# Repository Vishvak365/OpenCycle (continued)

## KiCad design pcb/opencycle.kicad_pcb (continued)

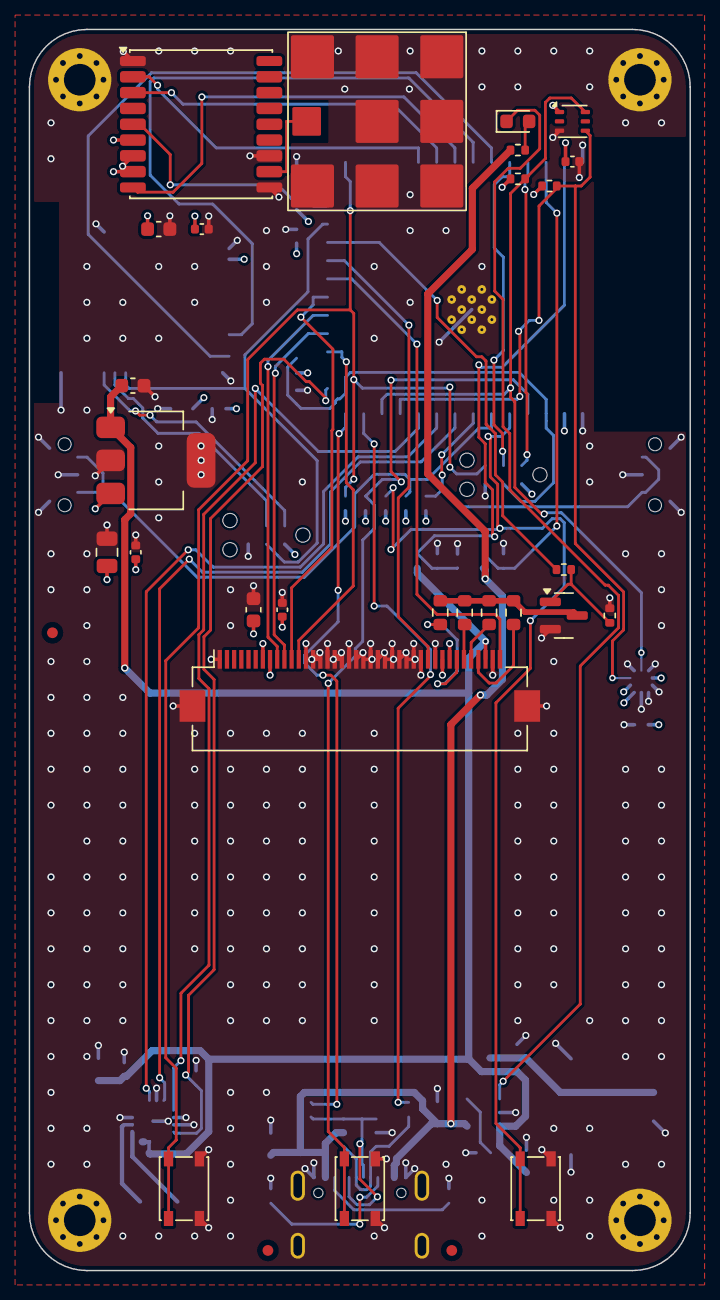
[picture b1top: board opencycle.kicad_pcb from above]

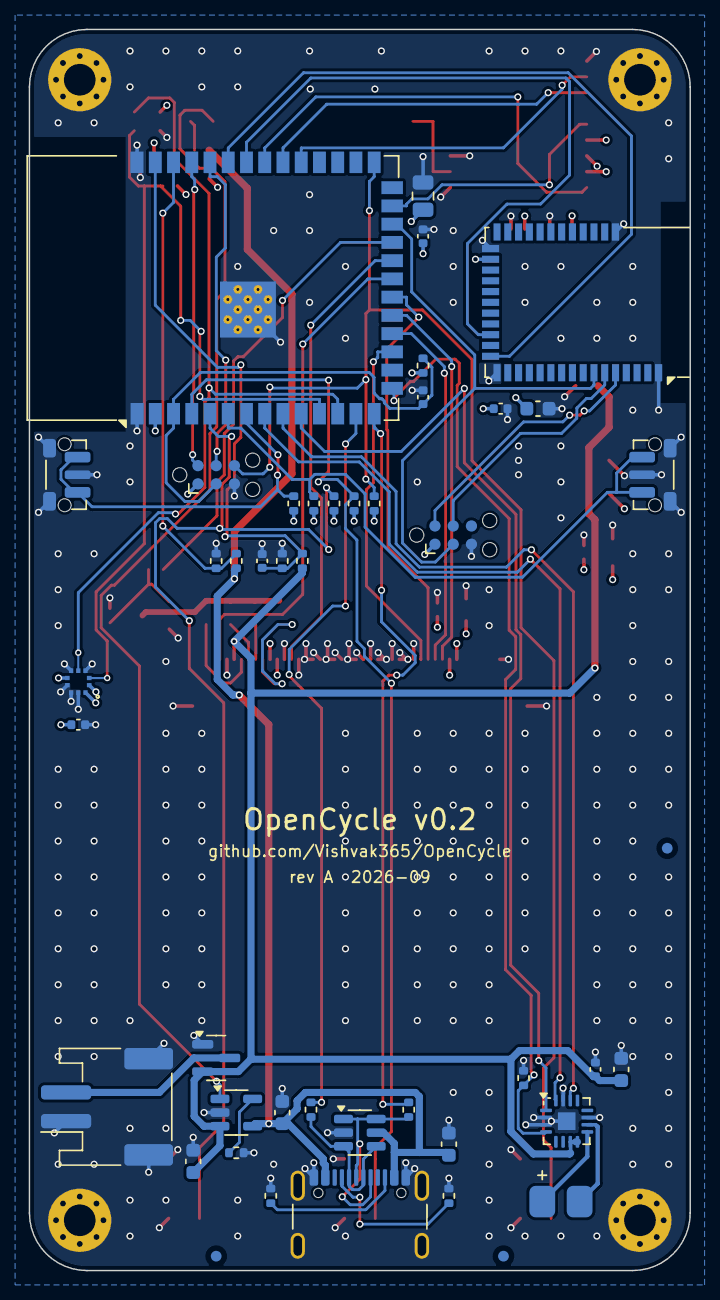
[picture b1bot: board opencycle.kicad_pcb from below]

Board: 4 copper layers, 46.0 x 86.4 mm, 79 parts (45 on the bottom side), 55 nets.

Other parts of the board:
FID1, FID2, FID3, FID4, FID5, FID6: Fiducial; Fiducial_0.75mm_Mask1.5mm
H1, H2, H3, H4: MountingHole_2.2mm_M2_Pad_Via

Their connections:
GND: H1.1, H2.1, H3.1, H4.1; also elsewhere on the board

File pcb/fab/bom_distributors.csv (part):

Vendor,Vendor part number,Manufacturer,MPN,Description,Qty per board,Qty to order (5 boards),Unit price USD,Line total (1 board),Price checked,Stock seen,Designators,Link,Datasheet
Mouser,485-258,,,"Adafruit 258 LiPo 1200 mAh 34 x 62 x 5 mm, protected, JST-PH",1,5,9.95,9.95,2026-09-30,,"checked 2026-09-30, 388 in stock",,
Mouser,621-AP7361C-33E-13,Diodes,AP7361C-33E-13,"3.3 V 1 A LDO, SOT-223",1,5,0.52,0.52,2026-09-30,733,U5,https://www.mouser.com/c/?q=621-AP7361C-33E-13,https://www.diodes.com/assets/Datasheets/AP7361C.pdf
Mouser,239-BL652-SA-01-T/R,Ezurio,BL652-SA-01-T/R,"Ezurio (Laird) BL652, nRF52832 module, integrated antenna",1,5,10.40,10.40,2026-09-30,5583,U2,https://www.mouser.com/c/?q=239-BL652-SA-01-T/R,https://www.ezurio.com/wireless-modules/bluetooth-modules/bl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
Mouser,187-CL05A105KO5NNNC,Samsung,CL05A105KO5NNNC,1 uF 16 V X5R 0402,1,7,0.10,0.10,typical,,C3,https://www.mouser.com/c/?q=187-CL05A105KO5NNNC,
Mouser,187-CL05B104KO5NNNC,Samsung,CL05B104KO5NNNC,100 nF 16 V X7R 0402,9,47,0.10,0.90,typical,,C2 C5 C7 C8 C10 C13 C17 C19 C20,https://www.mouser.com/c/?q=187-CL05B104KO5NNNC,
Mouser,187-CL10A106KP8NNNC,Samsung,CL10A106KP8NNNC,10 uF 10 V X5R 0603,5,27,0.12,0.60,typical,,C4 C6 C9 C11 C18,https://www.mouser.com/c/?q=187-CL10A106KP8NNNC,
Mouser,187-CL10A475KO8NNNC,Samsung,CL10A475KO8NNNC,4.7 uF 16 V X5R 0603,3,17,0.10,0.30,typical,,C14 C15 C16,https://www.mouser.com/c/?q=187-CL10A475KO8NNNC,
Mouser,187-CL21A226MAQNNNE,Samsung,CL21A226MAQNNNE,22 uF 25 V X5R 0805,2,12,0.22,0.44,typical,,C1 C12,https://www.mouser.com/c/?q=187-CL21A226MAQNNNE,
Mouser,490-CMS151125078L100,Same Sky,CMS-151125-078L100,"Same Sky 15 x 11 x 2.5 mm speaker, 8 ohm 0.7 W, IP67, wire leads",1,5,2.96,2.96,2026-09-30,597,LS1,https://www.mouser.com/c/?q=490-CMS151125078L100,https://www.mouser.com/datasheet/3/6118/1/cms-151125-078x-67.pdf
Mouser,621-DMG2302UK-7,Diodes,DMG2302UK-7,N-MOSFET 20 V SOT-23 (backlight PWM),1,7,0.39,0.39,2026-09-30,238766,Q1,https://www.mouser.com/c/?q=621-DMG2302UK-7,https://www.diodes.com/assets/Datasheets/DMG2302UK.pdf
Mouser,356-ESP32S3WRM1N16R8,Espressif,ESP32-S3-WROOM-1-N16R8,"ESP32-S3 module, 16 MB flash, 8 MB octal PSRAM, PCB antenna",1,5,6.72,6.72,2026-09-30,47727,U1,https://www.mouser.com/c/?q=356-ESP32S3WRM1N16R8,https://www.espressif.com/sites/default/files/documentation/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
Mouser,798-FH12-40S-0.5SH55,Hirose,FH12-40S-0.5SH(55),Hirose 40-pin 0.5 mm bottom-contact FFC connector,1,5,2.50,2.50,2026-09-30,25967,J3,https://www.mouser.com/c/?q=798-FH12-40S-0.5SH55,https://www.hirose.com/product/series/FH12
Mouser,859-LTR-303ALS-01,Lite-On,LTR-303ALS-01,"Lite-On ambient light sensor, I2C",1,5,0.68,0.68,2026-09-30,29622,U4,https://www.mouser.com/c/?q=859-LTR-303ALS-01,https://optoelectronics.liteon.com/upload/download/DS86-2013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
Mouser,859-LTST-C191KGKT,Lite-On,LTST-C191KGKT,Green LED 0603,1,7,0.15,0.15,2026-09-30,1190000,D1,https://www.mouser.com/c/?q=859-LTST-C191KGKT,https://optoelectronics.liteon.com/upload/download/DS22-2000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
Mouser,377-MAX-M10S-00B,u-blox,MAX-M10S-00B,"u-blox M10 GNSS module, LCC-18",1,5,9.12,9.12,2026-09-30,2746,U3,https://www.mouser.com/c/?q=377-MAX-M10S-00B,https://content.u-blox.com/sites/default/files/MAX-M10S_Data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
Mouser,700-MAX98357AETE+T,Analog Devices,MAX98357AETE+T,"I2S class-D amplifier, TQFN-16",1,5,4.08,4.08,2026-09-30,10971,U7,https://www.mouser.com/c/?q=700-MAX98357AETE+T,https://www.analog.com/media/en/technical-documentation/data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
Mouser,579-MCP73831T-2ACIOT,Microchip,MCP73831T-2ACI/OT,"Li-ion charger 4.20 V, SOT-23-5",1,5,0.76,0.76,2026-09-30,116042,U6,https://www.mouser.com/c/?q=579-MCP73831T-2ACIOT,https://ww1.microchip.com/downloads/en/DeviceDoc/MCP73831-Fa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
Mouser,763-24240320AFCSXP,Newhaven Display,NHD-2.4-240320AF-CSXP,"Newhaven 2.4 in IPS TFT 240 x 320, ST7789, 1200 nit, 40-pin FFC",1,5,15.86,15.86,2026-09-30,1032,"(display, plugs into J3)",https://www.mouser.com/c/?q=763-24240320AFCSXP,https://newhavendisplay.com/content/specs/NHD-2.4-240320AF-CSXP.pdf
Mouser,611-PTS810SJM250SMTR,C&K,PTS810 SJM 250 SMTR LFS,C&K top-actuated tact switch 4.2 x 3.2 x 2.5 mm,3,15,0.52,1.56,2026-09-30,30244,SW1 SW2 SW3,https://www.mouser.com/c/?q=611-PTS810SJM250SMTR,https://www.ckswitches.com/media/1476/pts810.pdf
Mouser,603-RC0402FR-07100KL,Yageo,RC0402FR-07100KL,Yageo resistor 100k 0402,4,22,0.10,0.40,typical,,R10 R18 R19 R20,https://www.mouser.com/c/?q=603-RC0402FR-07100KL,
Mouser,603-RC0402FR-07100RL,Yageo,RC0402FR-07100RL,Yageo resistor 100R 0402,1,7,0.10,0.10,typical,,R9,https://www.mouser.com/c/?q=603-RC0402FR-07100RL,
Mouser,603-RC0402FR-0710KL,Yageo,RC0402FR-0710KL,Yageo resistor 10k 0402,6,32,0.10,0.60,typical,,R1 R21 R22 R23 R24 R25,https://www.mouser.com/c/?q=603-RC0402FR-0710KL,
Mouser,603-RC0402FR-071KL,Yageo,RC0402FR-071KL,Yageo resistor 1k 0402,1,7,0.10,0.10,typical,,R2,https://www.mouser.com/c/?q=603-RC0402FR-071KL,
Mouser,603-RC0402FR-071ML,Yageo,RC0402FR-071ML,Yageo resistor 1M 0402,2,12,0.10,0.20,typical,,R16 R17,https://www.mouser.com/c/?q=603-RC0402FR-071ML,
Mouser,603-RC0402FR-072KL,Yageo,RC0402FR-072KL,Yageo resistor 2k 0402,1,7,0.10,0.10,typical,,R15,https://www.mouser.com/c/?q=603-RC0402FR-072KL,
Mouser,603-RC0402FR-074K7L,Yageo,RC0402FR-074K7L,Yageo resistor 4.7k 0402,2,12,0.10,0.20,typical,,R3 R4,https://www.mouser.com/c/?q=603-RC0402FR-074K7L,
Mouser,603-RC0402FR-075K1L,Yageo,RC0402FR-075K1L,Yageo resistor 5.1k 0402,2,12,0.10,0.20,typical,,R11 R12,https://www.mouser.com/c/?q=603-RC0402FR-075K1L,
Mouser,603-RC0402JR-070RL,Yageo,RC0402JR-070RL,Yageo resistor 0R 0402,2,12,0.10,0.20,typical,,R13 R14,https://www.mouser.com/c/?q=603-RC0402JR-070RL,
Mouser,603-RC0603FR-0733RL,Yageo,RC0603FR-0733RL,Yageo resistor 33R 0603,4,22,0.10,0.40,typical,,R5 R6 R7 R8,https://www.mouser.com/c/?q=603-RC0603FR-0733RL,
Mouser,306-S2BPHSM4TBLFSN,JST,S2B-PH-SM4-TB(LF)(SN),JST PH 2-pin side-entry SMT header,1,7,0.49,0.49,2026-09-30,269,J2,https://www.mouser.com/c/?q=306-S2BPHSM4TBLFSN,https://www.jst-mfg.com/product/pdf/eng/ePH.pdf
Mouser,688-SKRTLA,Alps Alpine,SKRTLAE010,Alps side-actuated tact switch,2,12,0.34,0.68,2026-09-30,2396,SW4 SW5,https://www.mouser.com/c/?q=688-SKRTLA,https://tech.alpsalpine.com/e/products/detail/SKRTLAE010/
Mouser,640-USB4105-GF-A,GCT,USB4105-GF-A,"GCT USB-C receptacle, USB 2.0, top mount",1,5,0.80,0.80,2026-09-30,420427,J1,https://www.mouser.com/c/?q=640-USB4105-GF-A,https://gct.co/files/drawings/usb4105.pdf
Mouser,511-USBLC6-2SC6,ST,USBLC6-2SC6,"USB ESD protection, SOT-23-6",1,7,0.49,0.49,2026-09-30,81014,D2,https://www.mouser.com/c/?q=511-USBLC6-2SC6,https://www.st.com/resource/en/datasheet/usblc6-2.pdf
Digi-Key,828-BMP581CT-ND,Bosch,BMP581,"Bosch barometric pressure sensor, LGA-10 2 x 2 mm",1,5,3.07,3.07,2026-09-30,462,U8,https://www.digikey.com/en/products/result?keywords=828-BMP581CT-ND,https://www.bosch-sensortec.com/media/boschsensortec/downloa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
Digi-Key,DMG2305UX-7DICT-ND,Diodes,DMG2305UX-7,P-MOSFET 20 V 4.2 A SOT-23 (reverse battery),1,7,0.30,0.30,2026-09-30,75458,Q2,https://www.digikey.com/en/products/result?keywords=DMG2305U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,https://www.diodes.com/assets/Datasheets/DMG2305UX.pdf
Digi-Key,DSGP.1575.12.4.A.02,Taoglas,DSGP.1575.12.4.A.02,"Taoglas 12 x 12 x 4 mm GPS L1 / Galileo E1 ceramic patch, SMT",1,5,4.25,4.25,2026-09-30,1474,AE1,https://www.digikey.com/en/products/result?keywords=DSGP.157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,https://www.taoglas.com/datasheets/DSGP.1575.12.4.A.02.pdf
SendCutSend / Ponoko,cad/out/stl/cover_lens.step,,,"1.0 mm clear acrylic or polycarbonate cover lens, 48.0 x 75.9 mm, 5 mm corner radius",1,5,3.00,3.00,estimate,,"black mask: vinyl or paint on the inside, window per cad/out/stl/lens_mask.stl",,
any,e.g. McMaster 92000A017,,,M2 x 5 mm pan-head screws (stainless),4,20,0.10,0.40,estimate,,PCB to back shell,,
any,,,,M2 x 6 mm pan-head screws (stainless),4,20,0.10,0.40,estimate,,front bezel to back shell (through the corner posts),,
any,,,,"Closed-cell foam tape 0.5 mm, 2 mm strips",1,5,1.00,1.00,estimate,,display gasket,,
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
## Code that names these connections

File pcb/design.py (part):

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# ============================================================ main MCU (back, antenna at the right edge)
ESP_PINS = {
    "GND": "GND", "3V3": "+3V3", "EN": "ESP_EN",
    "IO0": "KEY_L",            # strapping: low at reset = download mode (hold left key)
    "IO1": "VBAT_SENSE", "IO2": "VBUS_SENSE",      # ADC1
    "IO3": "AMP_EN",           # strapping (JTAG source, ignored unless eFuse set); 100k pull-down
    "IO4": "KEY_C", "IO5": "KEY_R", "IO6": "BTN_PWR", "IO7": "BTN_MENU",   # RTC GPIOs: wake from deep sleep
    "IO8": "I2C_SDA", "IO18": "I2C_SCL",
    "IO9": "LCD_DC", "IO10": "LCD_CS", "IO11": "LCD_MOSI", "IO12": "LCD_SCK",   # FSPI IO_MUX pins
    "IO13": "LCD_TE", "IO14": "LCD_RST", "IO21": "LCD_BL",
    "IO15": "I2S_BCLK", "IO16": "I2S_LRCLK", "IO17": "I2S_DIN",
    "IO19": "USB_DN", "IO20": "USB_DP",
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part("U2", "BL652-SA-01", "RF_Bluetooth:BL652", "RF_Module:Laird_BL652", "B", 11.05, 22.0, 180, {
    "GND": "GND", "VDD": "+3V3", "SWDIO": "BLE_SWDIO", "SWDCLK": "BLE_SWDCLK",
    "SIO_21": "BLE_RST",       # nRF52832 P0.21 = nRESET
    "SIO_06": "BLE_TX", "SIO_08": "BLE_RX",       # module UART (Laird default TX/RX pins)
    **{k: None for k in ["SIO_24", "SIO_23", "SIO_22", "SIO_20", "SIO_18", "SIO_16", "SIO_14", "SIO_12", "SIO_11",
                         "SIO_10/NFC2", "SIO_09/NFC1", "SIO_07", "SIO_05/AIN3", "SIO_04/AIN2", "SIO_03/AIN1",
                         "SIO_02/AIN0", "SIO_01", "SIO_00", "SIO_13", "SIO_15", "SIO_17", "SIO_19",
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
# ============================================================ display (front, FFC folded behind the panel)
DISP = {"Pin_1": "GND", "Pin_2": None, "Pin_3": None, "Pin_4": None, "Pin_5": None, "Pin_6": None,
        "Pin_7": "+3V3", "Pin_8": "+3V3", "Pin_9": "LCD_MOSI", "Pin_10": "LCD_CS", "Pin_11": "LCD_SCK",
        "Pin_12": "LCD_DC", "Pin_13": "GND", "Pin_30": "LCD_RST", "Pin_31": "GND", "Pin_32": "+3V3", "Pin_33": "+3V3",
        "Pin_34": "LED_K1", "Pin_35": "LED_K2", "Pin_36": "LED_K3", "Pin_37": "LED_K4", "Pin_38": "VBAT",
        "Pin_39": "GND", "Pin_40": "LCD_TE", "MountPin": "GND"}
DISP.update({f"Pin_{i}": "GND" for i in range(14, 30)})      # DB0-DB15 unused in SPI mode
part("J3", "FH12-40S-0.5SH(55)", "Connector_Generic_MountingPin:Conn_01x40_MountingPin",
     "Connector_FFC-FPC:Hirose_FH12-40S-0.5SH_1x40-1MP_P0.50mm_Horizontal", "F", 26.0, 48.7, 0, DISP,
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    part(ref, "PTS810", "Switch:SW_Push", "Button_Switch_SMD:SW_SPST_PTS810", "F", x, KEY_Y, 90, {"1": net, "2": "GND"},
         f"Front soft key ({net}). Top-actuated, 2.5 mm tall. Turned 90 deg so the USB-C locating pegs clear its pads.", "PTS810 SJM 250 SMTR LFS", "C&K", 2.5)
part("SW4", "SKRTLAE010", "Switch:SW_Push", "Button_Switch_SMD:SW_Push_1P1T-MP_NO_Horizontal_Alps_SKRTLAE010", "B",
     5.45, 34.0, 90, {"1": "BTN_PWR", "2": "GND"}, "Left side: power / back", "SKRTLAE010", "Alps Alpine", 3.55)
part("SW5", "SKRTLAE010", "Switch:SW_Push", "Button_Switch_SMD:SW_Push_1P1T-MP_NO_Horizontal_Alps_SKRTLAE010", "B",
     46.55, 34.0, -90, {"1": "BTN_MENU", "2": "GND"}, "Right side: menu", "SKRTLAE010", "Alps Alpine", 3.55)
R("R21", "10k", "B", 25.0, 36.0, 90, "+3V3", "KEY_L", "Key pull-ups")
R("R22", "10k", "B", 26.4, 36.0, 90, "+3V3", "KEY_C")
R("R23", "10k", "B", 27.8, 36.0, 90, "+3V3", "KEY_R")
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
# ============================================================ ESP32 console / recovery (Tag-Connect footprint, back)
part("J5", "Console", "Connector_Generic:Conn_01x06", "Connector:Tag-Connect_TC2030-IDC-NL_2x03_P1.27mm_Vertical", "B",
     36.0, 34.0, 0, {"Pin_1": "+3V3", "Pin_2": "CON_TX", "Pin_3": "ESP_EN", "Pin_4": "CON_RX", "Pin_5": "GND",
                     "Pin_6": "KEY_L"},
     "ESP32 UART0 + EN + IO0 for recovery (normal flashing is over USB-C). Nothing to assemble.", "", "", 0.0)

# ============================================================ fiducials (3 per side, for machine assembly)
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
